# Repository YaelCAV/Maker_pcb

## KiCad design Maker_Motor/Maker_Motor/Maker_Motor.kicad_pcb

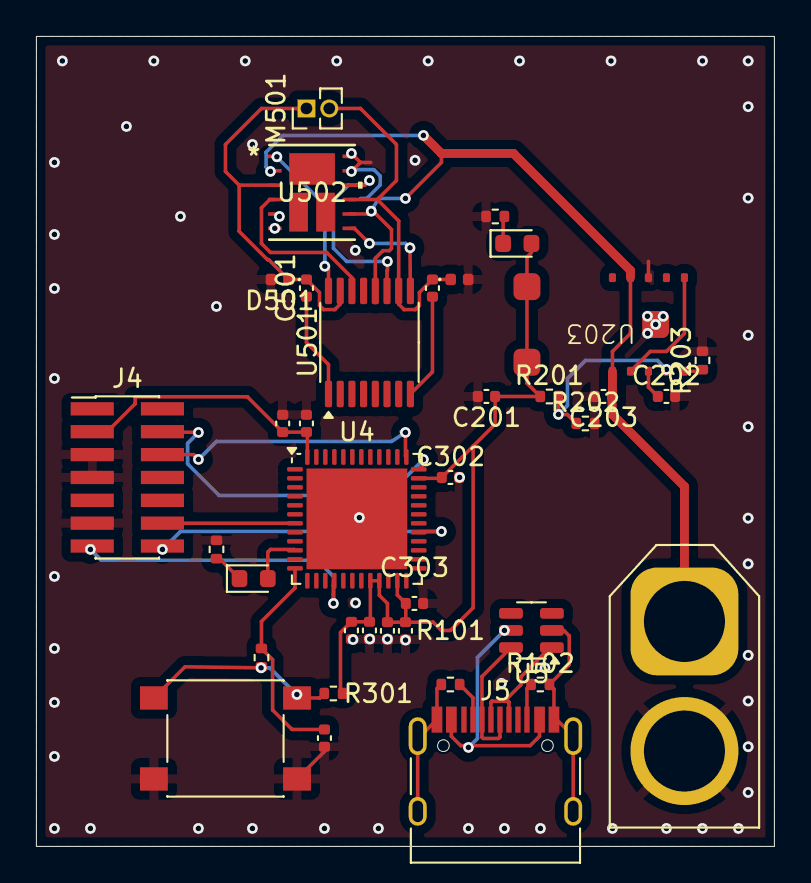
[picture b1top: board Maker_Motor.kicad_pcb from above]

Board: 2 copper layers, 41.0 x 45.0 mm, 37 parts (0 on the bottom side), 31 nets.

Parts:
C201, C202, C203, C501, C502: C; C_0402_1005Metric
C301, C302, C303, C307, C310: 100n; C_0402_1005Metric
C305: 4.7u; C_0402_1005Metric
C306: 10n; C_0402_1005Metric
C308, C309: 1u; C_0402_1005Metric
D201, D301: LED; LED_0603_1608Metric
D501, D502: D_Zener; D_0402_1005Metric
J4: Conn_ST_STDC14; PinHeader_2x07_P1.27mm_Vertical_SMD
J5: USB_C_Receptacle_USB2.0_16P; USB_C_Receptacle_HRO_TYPE-C-31-M-12
J201: Conn_01x02_Pin; AMASS_XT60-F_1x02_P7.20mm_Vertical
M501: Motor_DC; PinHeader_1x02_P1.27mm_Vertical
R101, R102: 5.1k; R_0402_1005Metric
R201: 402K; R_0402_1005Metric
R202: 80; R_0402_1005Metric
R203: R; R_0402_1005Metric
R204, R301, R302, R303: 10k; R_0402_1005Metric
SW301: SW_Push; SW_Push_1P1T_NO_6x6mm_H9.5mm
U4: STM32G431CBUx; QFN-48-1EP_7x7mm_P0.5mm_EP5.6x5.6mm
U5: USBLC6-2SC6; SOT-23-6
U203: 171013801
U501: TSSOP-16_4.4x5mm_P0.65mm
U502: MLP_4P5X5_ONS-L

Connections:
+3.3V: C201.1, C301.1, C302.1, C303.1, C305.1, C306.1, C307.1, C308.1, C309.1, D201.2 (A), J4.3 (VCC), R201.1, R301.1, U4.20 (VREF+), U4.21 (VDDA), U4.23 (VDD), U4.35 (VDD), U4.48 (VDD), U203.7 (VOUT)
/CPU/BTN: C310.1, R302.1, U4.12 (PA4)
/CPU/LED: D301.2 (A), U4.10 (PA2)
/CPU/NRST: J4.12 (~RST), U4.7 (PG10)
/CPU/RX: J4.13 (VCP_RX), U4.16 (PC4)
/CPU/SWCLK: J4.6 (JCLK/SWCLK), U4.37 (PA14)
/CPU/SWDIO: J4.4 (JTMS/SWDIO), U4.36 (PA13)
/CPU/TX: J4.14 (VCP_TX), U4.29 (PC6)
/Motor/AHO: U501.9 (AHO), U502.7 (G4)
/Motor/AHS: C502.2, D502.1 (K), M501.2 (-), U501.10 (AHS), U502.9 (D3/S4)
/Motor/ALO: U501.11 (ALO), U502.10 (G3)
/Motor/BHO: U501.16 (BHO), U502.1 (G1)
/Motor/BHS: C501.2, D501.1 (K), M501.1 (+), U501.15 (BHS), U502.3 (S1/D2)
/Motor/BLO: U501.14 (BLO), U502.4 (G2)
/PSU/VBAT: C203.1, J201.1, U203.5 (VIN), U501.12 (VDD), U502.2 (D1/D4), U502.8 (D1/D4)
/USB/D+: J5.A6 (D+), J5.B6 (D+), U5.1 (I/O1)
/USB/D-: J5.A7 (D-), J5.B7 (D-), U5.6 (I/O1)
/USB/ISO_GND: J5.A1 (GND), J5.A12 (GND), J5.B1 (GND), J5.B12 (GND), J5.S1 (SHIELD), R101.2, R102.2, U5.2 (GND)
/USB/V_USB: J5.A4 (VBUS), J5.A9 (VBUS), J5.B4 (VBUS), J5.B9 (VBUS), U5.5 (VBUS)
GND: C201.2, C202.2, C203.2, C301.2, C302.2, C303.2, C305.2, C306.2, C307.2, C308.2, C309.2, C310.2, D501.2 (A), D502.2 (A), J4.5 (GND), J4.7 (GND), J4.11 (GNDDetect), J201.2, R202.2, R203.2, R204.1, R303.1, SW301.2, U4.49 (VSS), U203.10 (AGND), U203.13 (PGND), U502.5 (S2), U502.6 (S2), U502.11 (S3), U502.12 (S3)
unnamed: D201.1 (K), R204.2
unnamed: D301.1 (K), R303.2
unnamed: J5.A5 (CC1), R101.1
unnamed: J5.B5 (CC2), R102.1
unnamed: R301.2, R302.2, SW301.1
unnamed: U203.4 (VIN), U203.12 (EN)
unnamed: R201.2, R202.1, U203.2 (FB)
unnamed: R203.1, U203.1 (FSW)
unnamed: C202.1, U203.3 (VCC)
unnamed: C502.1, U501.8 (AHB)
unnamed: C501.1, U501.1 (BHB)

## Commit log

2025-02-02 first commit copy
